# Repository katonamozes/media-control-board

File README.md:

# Media Control Board

A custom 5-key macropad with a rotary encoder, an OLED display, and RGB indicators, powered by a Seeed XIAO RP2040.

BOM:
Everything that you need in order to make this hackpad
1x Seeed Studio XIAO RP2040
5x mechanical switches
1x rotary encoder with push-button
1x 0.91" I2C OLED
4x SK6812MINI-E RGB LEDs
1x Case (2 3d printed parts)
4x M3 bolts

The button connected to pin 10 plays the previous track.
The button connected to pin 8 plays the next track.
The button connected to pin 9 pauses the media.
The button connected to pin 7 scrolls right.
The button connected to pin 11 scrolls left.

The rotary encoder's button is connected to pin 6 and mutes.
The Rotary encoder's rotation is connected to pin 4 and 5 and controls the volume.

The sk6812MINI-E leds are connected to pin 1.

The 0.91 inch OLED display is connected to pins 2(SCL) and 3(SDA).

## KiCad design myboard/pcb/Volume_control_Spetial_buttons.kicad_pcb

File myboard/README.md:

# Media Control Board

A custom 5-key macropad with a rotary encoder, an OLED display, and RGB indicators, powered by a Seeed XIAO RP2040.

BOM:
Everything that you need in order to make this hackpad
1x Seeed Studio XIAO RP2040
5x mechanical switches
1x rotary encoder with push-button
1x 0.91" I2C OLED
4x SK6812MINI-E RGB LEDs
1x Case (2 3d printed parts)
4x M3 bolts

The button connected to pin 10 plays the previous track.
The button connected to pin 8 plays the next track.
The button connected to pin 9 pauses the media.
The button connected to pin 7 scrolls right.
The button connected to pin 11 scrolls left.

The rotary encoder's button is connected to pin 6 and mutes.
The Rotary encoder's rotation is connected to pin 4 and controls the volume.

The sk6812MINI-E leds are connected to pin 1.

The 0.91 inch OLED display is connected to pins 2(SCL) and 3(SDA).

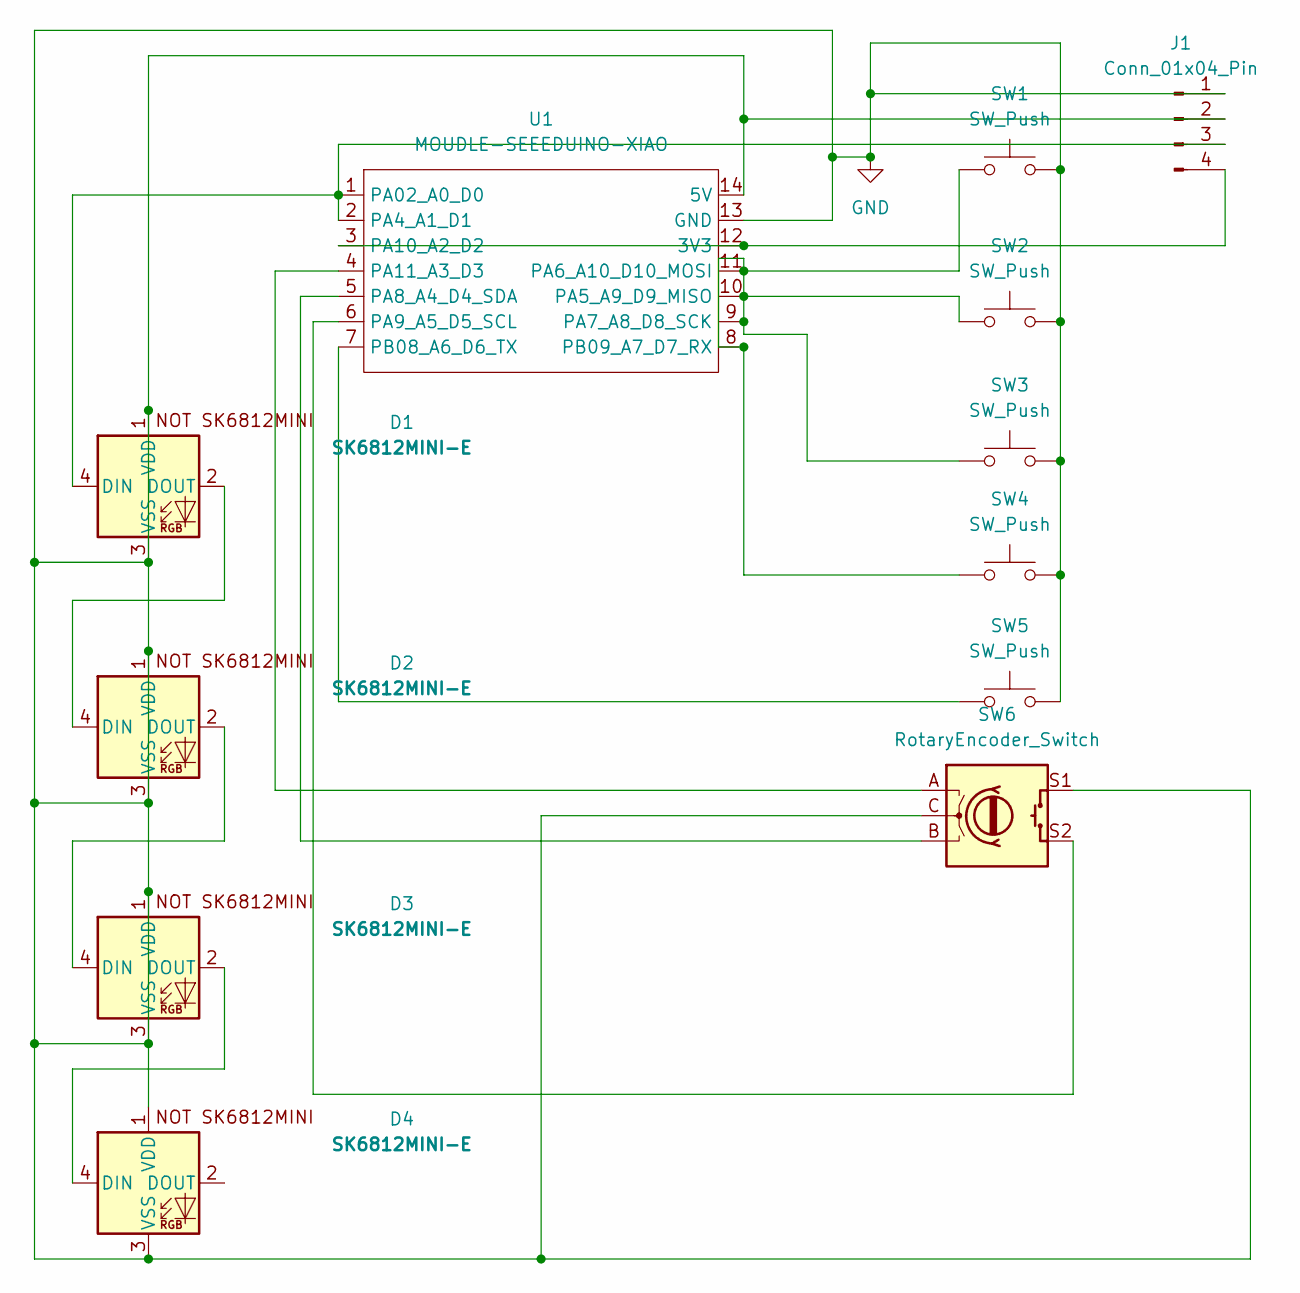
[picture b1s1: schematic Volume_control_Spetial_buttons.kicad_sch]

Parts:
D1, D2, D3, D4: SK6812MINI-E; SK6812MINI-E_fixed
J1: Conn_01x04_Pin; PinHeader_1x04_P2.54mm_Vertical
SW1, SW2, SW3, SW4, SW5: SW_Push; SW_Cherry_MX_1.00u_PCB
SW6: RotaryEncoder_Switch; RotaryEncoder_Alps_EC11E-Switch_Vertical_H20mm
U1: MOUDLE-SEEEDUINO-XIAO; XIAO-Generic-Hybrid-14P-2.54-21X17.8MM

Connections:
GND: D1.1 (VDD), D1.3 (VSS), D2.1 (VDD), D2.3 (VSS), D3.1 (VDD), D3.3 (VSS), D4.1 (VDD), D4.3 (VSS), J1.1, J1.2, SW1.2, SW2.2, SW3.2, SW4.2, SW5.2, SW6.C, SW6.S1, U1.13 (GND), U1.14 (5V)
unnamed: D1.4 (DIN), J1.3, U1.1 (PA02_A0_D0), U1.2 (PA4_A1_D1)
unnamed: D1.2 (DOUT), D2.4 (DIN)
unnamed: D2.2 (DOUT), D3.4 (DIN)
unnamed: D3.2 (DOUT), D4.4 (DIN)
unnamed: J1.4, U1.3 (PA10_A2_D2), U1.12 (3V3)
unnamed: SW1.1, SW2.1, SW3.1, SW4.1, U1.8 (PB09_A7_D7_RX), U1.9 (PA7_A8_D8_SCK), U1.10 (PA5_A9_D9_MISO), U1.11 (PA6_A10_D10_MOSI)
unnamed: SW6.B, U1.5 (PA8_A4_D4_SDA)
unnamed: SW6.S2, U1.6 (PA9_A5_D5_SCL)
unnamed: SW6.A, U1.4 (PA11_A3_D3)
unnamed: SW5.1, U1.7 (PB08_A6_D6_TX)

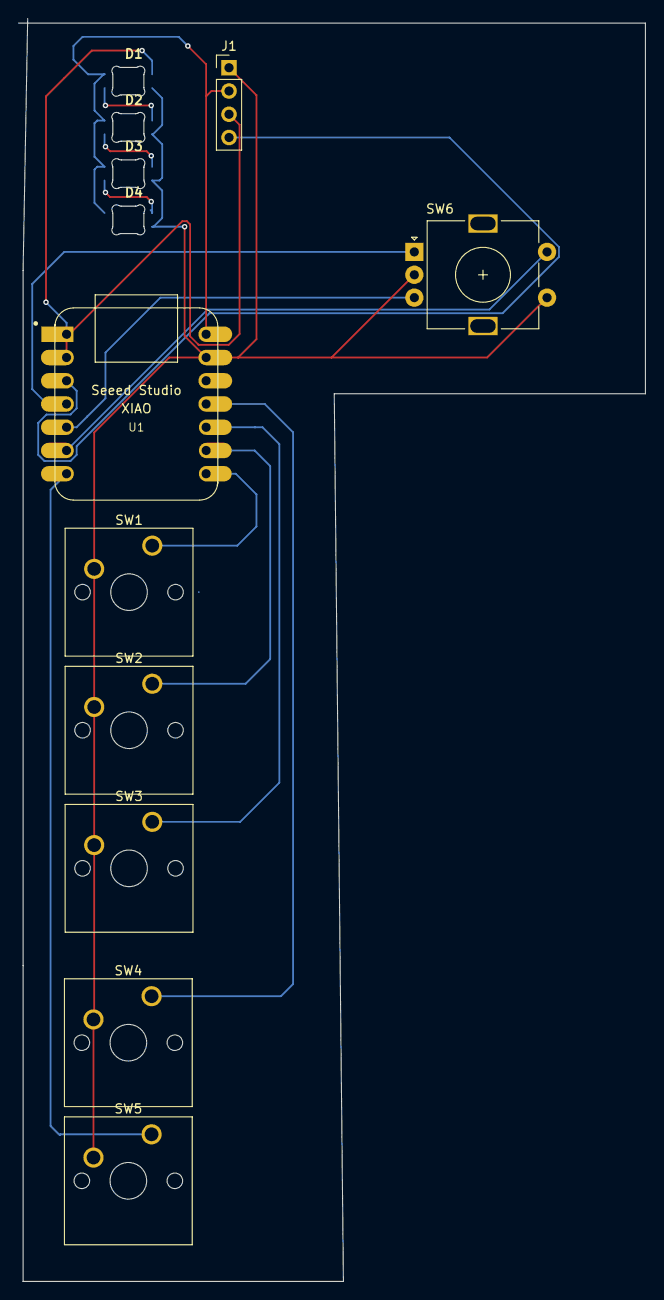
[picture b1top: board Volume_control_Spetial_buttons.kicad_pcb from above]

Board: 2 copper layers, 68.5 x 138.0 mm, 12 parts (0 on the bottom side), 11 nets.

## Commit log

2026-02-28 Enhance README with images and BOM details
    Added images and updated BOM section in README.
2026-02-28 Add images to README for better visualization
    Added images to enhance the README documentation.
2026-02-28 Clarify rotary encoder pin connections in README
    Updated the pin connections for the rotary encoder's rotation.
